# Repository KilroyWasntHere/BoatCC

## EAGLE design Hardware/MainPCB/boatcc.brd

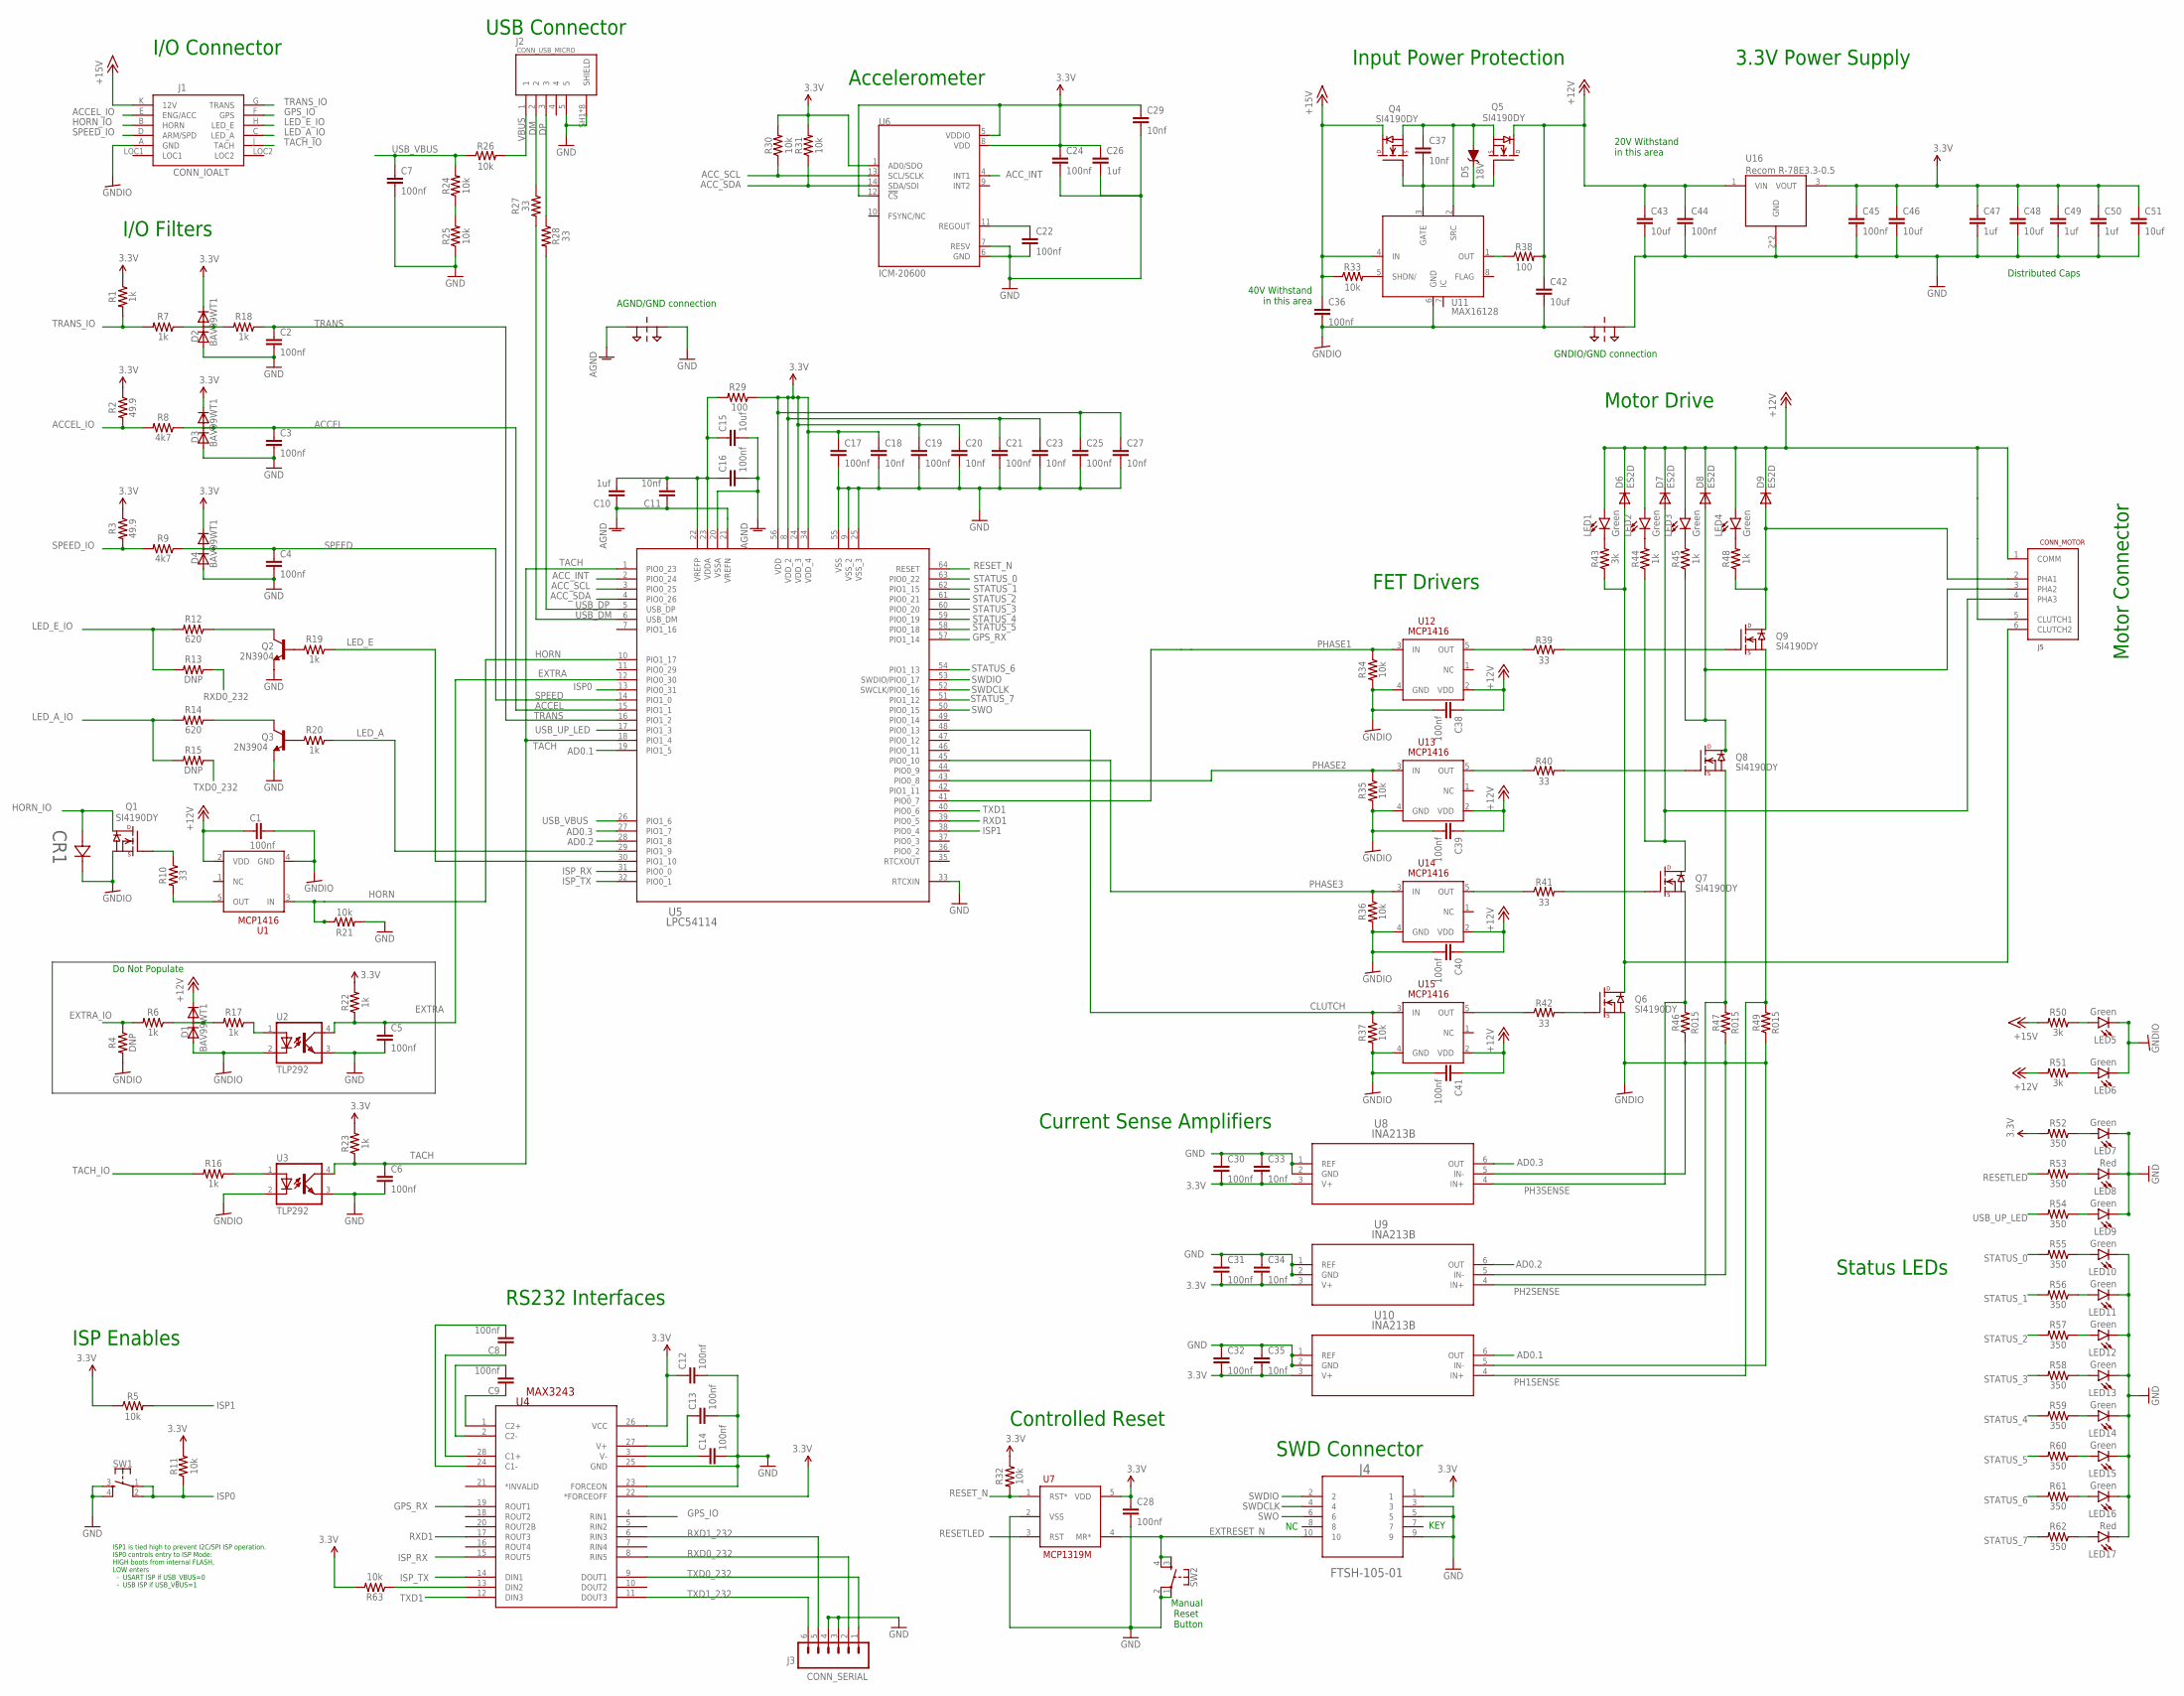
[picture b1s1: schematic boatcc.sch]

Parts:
C1, C2, C3, C4, C5, C6, C7, C8, C9, C12, C13, C14, C16, C17, C19, C21, C22, C24, C25, C28, C30, C31, C32, C36, C38, C39, C40, C41, C44, C45: 100nf; 0805
C10, C26, C47, C49, C50: 1uf; 0805
C11, C18, C20, C23, C27, C29, C33, C34, C35, C37: 10nf; 0805
C15, C42, C43, C46, C48, C51: 10uf; 0805
CR1: SMAJ45CASMASERIES-M; SMASERIES-M; MANUFACTURER_PART_NUMBER SMAJ24CA; DIGI-KEY_PART_NUMBER SMAJ24CALFCT-ND
D1, D2, D3, D4: BAV99WT1; SC70
D5: 18V; SOD-323
D6, D7, D8, D9: ES2D; SMB
J1: CONN_IOALT; CONN_IO
J2: CONN_USB_MICRO; MOLEX_1050170001
J3: CONN_SERIAL; 1X06_LOCK
J4: FTSH-105-01; SAMTEC-FTSH-105-01-X-DV
J5: CONN_MOTOR
LED1, LED2, LED3, LED4, LED5, LED6, LED7, LED9, LED10, LED11, LED12, LED13, LED14, LED15, LED16: Green; LED_0805; DIGI-KEY_PART_NUMBER 732-4986-1-ND
LED8, LED17: Red; LED_0805; DIGI-KEY_PART_NUMBER 732-4984-1-ND
Q1, Q4, Q5, Q6, Q7, Q8, Q9: SI4190DY; SO-8
Q2, Q3: 2N3904; SOT23-3
R1, R6, R7, R16, R17, R18, R19, R20, R22, R23, R44, R45, R48: 1k; 0805
R2, R3: 49.9; 0805
R4, R13, R15: DNP; 0805
R5, R11, R21, R24, R25, R26, R30, R31, R32, R33, R34, R35, R36, R37, R63: 10k; 0805
R8, R9: 4k7; 0805
R10, R27, R28, R39, R40, R41, R42: 33; 0805
R12, R14: 620; 0805
R29, R38: 100; 0805
R43, R50, R51: 3k; 0805
R46, R47, R49: R015; 1206; DIGI-KEY_PART_NUMBER 408-1572-1-ND
R52, R53, R54, R55, R56, R57, R58, R59, R60, R61, R62: 350; 0805
SUPPLY1, SUPPLY2: 2PT_GND_TIE
SW1, SW2: MOMENTARY-SWITCH-SPST-2-SMD-5.2MM; TACTILE_SWITCH_SMD_5.2MM
U1, U12, U13, U14, U15: MCP1416; SOT-23-5_MC-M
U2, U3: TLP292; MINI-FLAT-4; DIGI-KEY_PART_NUMBER TLP292(GB-TPLECT-ND
U4: MAX3243; PW28-M
U5: LPC54114; LQFP64_10X10-M
U6: ICM-20600; PQFN50P250X300X97-14N
U7: MCP1319M; SOT23-5
U8, U9, U10: INA213B; DCK6-M; MANUFACTURER_PART_NUMBER INA213BIDCKR; DIGI-KEY_PART_NUMBER 296-40129-1-ND
U11: MAX16128; UMAX8; MOUSER_PART_NUMBER 700-MAX16128UAACAC+T
U16: Recom R-78E3.3-0.5; D2PACK/A; DIGI-KEY_PART_NUMBER 497-5225-1-ND

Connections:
3.3V: C12.1, C17.1, C18.1, C19.1, C20.1, C21.1, C23.1, C24.1, C25.1, C26.1, C27.1, C28.1, C29.1, C30.2, C31.2, C32.2, C33.2, C34.2, C35.2, C45.1, C46.1, C47.1, C48.1, C49.1, C50.1, C51.1, D2.2 (C), D3.2 (C), D4.2 (C), J4.1, R1.1, R2.1, R3.1, R5.1, R11.2, R22.2, R23.2, R29.1, R30.2, R31.2, R32.1, R52.2, R63.2, U4.22 (*FORCEOFF), U4.26 (VCC), U5.8 (VDD_2), U5.24 (VDD_3), U5.34 (VDD_4), U5.56 (VDD), U6.1 (AD0/SDO), U6.5 (VDDIO), U6.8 (VDD), U6.12 (!CS), U7.5 (VDD), U8.3 (V+), U9.3 (V+), U10.3 (V+), U16.3 (VOUT)
+12V: C1.1, C38.1, C39.1, C40.1, C41.1, C42.1, C43.1, C44.1, D1.2 (C), D6.C, D7.C, D8.C, D9.C, J5.1 (COMM), J5.5 (CLUTCH1), LED1.A, LED2.A, LED3.A, LED4.A, Q5.5 (D), Q5.6 (D), Q5.7 (D), Q5.8 (D), R38.2, R51.2, U1.2 (VDD), U12.2 (VDD), U13.2 (VDD), U14.2 (VDD), U15.2 (VDD), U16.1 (VIN)
+15V: C36.1, J1.K (12V), Q4.5 (D), Q4.6 (D), Q4.7 (D), Q4.8 (D), R33.1, R50.2, U11.4 (IN)
ACCEL: C3.1, D3.3 (AC), R8.1, U5.15 (PIO1_1)
ACCEL_IO: J1.E (ENG/ACC), R2.2, R8.2
ACC_INT: U5.2 (PIO0_24), U6.4 (INT1)
ACC_SCL: R30.1, U5.3 (PIO0_25), U6.13 (SCL/SCLK)
ACC_SDA: R31.1, U5.4 (PIO0_26), U6.14 (SDA/SDI)
AD0.1: U5.19 (PIO1_5), U10.6 (OUT)
AD0.2: U5.28 (PIO1_8), U9.6 (OUT)
AD0.3: U5.27 (PIO1_7), U8.6 (OUT)
AGND: C10.1, C11.1, C15.2, C16.2, SUPPLY1.P$1, U5.20 (VSSA), U5.21 (VREFN)
CLUTCH: R37.1, U5.48 (PIO0_13), U15.3 (IN)
CLUTCH2: D6.A, J5.6 (CLUTCH2), Q6.5 (D), Q6.6 (D), Q6.7 (D), Q6.8 (D), R43.1
DM: J2.2, R27.1
DP: J2.3, R28.1
EXTRA: C5.1, R22.1, U2.4 (COL), U5.12 (PIO0_30)
EXTRA_IO: R4.1, R6.2
EXTRESET_N: J4.10, SW2.3, SW2.4, U7.4 (MR*)
FILTER_IN1: D1.3 (AC), R6.1, R17.2
GND: C2.2, C3.2, C4.2, C5.2, C6.2, C7.2, C12.2, C13.2, C14.2, C17.2, C18.2, C19.2, C20.2, C21.2, C22.2, C23.2, C24.2, C25.2, C26.2, C27.2, C28.2, C29.2, C30.1, C31.1, C32.1, C33.1, C34.1, C35.1, C43.2, C44.2, C45.2, C46.2, C47.2, C48.2, C49.2, C50.2, C51.2, D2.1 (A), D3.1 (A), D4.1 (A), J2.5, J2.SH1 (SHIELD), J2.SH2 (SHIELD), J2.SH3 (SHIELD), J2.SH4 (SHIELD), J2.SH5 (SHIELD), J2.SH6 (SHIELD), J2.SH7 (SHIELD), J2.SH8 (SHIELD), J3.3, J3.4, J4.3, J4.5, J4.9, LED7.C, LED8.C, LED9.C, LED10.C, LED11.C, LED12.C, LED13.C, LED14.C, LED15.C, LED16.C, LED17.C, Q2.2 (E), Q3.2 (E), R21.2, R25.1, SUPPLY1.P$2, SUPPLY2.P$2, SW1.3, SW1.4, SW2.1, SW2.2, U2.3 (EMIT), U3.3 (EMIT), U4.23 (FORCEON), U4.25 (GND), U5.9 (VSS_2), U5.25 (VSS_3), U5.33 (RTCXIN), U5.55 (VSS), U6.6 (GND), U6.7 (RESV), U7.2 (VSS), U8.1 (REF), U8.2 (GND), U9.1 (REF), U9.2 (GND), U10.1 (REF), U10.2 (GND), U16.2 (GND), U16.TAB (GND)
GNDIO: C1.2, C36.2, C38.2, C39.2, C40.2, C41.2, C42.2, CR1.1 (2), D1.1 (A), J1.A (GND), LED5.C, LED6.C, Q1.1 (S), Q1.2 (S), Q1.3 (S), Q6.1 (S), Q6.2 (S), Q6.3 (S), R4.2, R34.2, R35.2, R36.2, R37.2, R46.1, R47.1, R49.1, SUPPLY2.P$1, U1.4 (GND), U2.2 (C), U3.2 (C), U8.5 (IN-), U9.5 (IN-), U10.5 (IN-), U11.6 (GND), U12.4 (GND), U13.4 (GND), U14.4 (GND), U15.4 (GND)
GPS_IO: J1.F (GPS), U4.4 (RIN1)
GPS_RX: U4.19 (ROUT1), U5.57 (PIO1_14)
HORN: R21.1, U1.3 (IN), U5.10 (PIO1_17)
HORN_IO: CR1.2 (1), J1.B (HORN), Q1.5 (D), Q1.6 (D), Q1.7 (D), Q1.8 (D)
INT_PWR: C37.1, D5.A, Q4.1 (S), Q4.2 (S), Q4.3 (S), Q5.1 (S), Q5.2 (S), Q5.3 (S), U11.2 (SRC)
ISP0: R11.1, SW1.1, SW1.2, U5.13 (PIO0_31)
ISP1: R5.2, U5.38 (PIO0_4)
ISP_RX: U4.15 (ROUT5), U5.31 (PIO0_0)
ISP_TX: U4.14 (DIN1), U5.32 (PIO0_1)
LED_A: R20.1, U5.29 (PIO1_9)
LED_A_IO: J1.C (LED_A), R14.2, R15.2
LED_E: R19.1, U5.30 (PIO1_10)
LED_E_IO: J1.H (LED_E), R12.2, R13.2
MOTOR_PHASE_1: D9.A, J5.2 (PHA1), Q9.5 (D), Q9.6 (D), Q9.7 (D), Q9.8 (D), R48.1
MOTOR_PHASE_2: D8.A, J5.3 (PHA2), Q8.5 (D), Q8.6 (D), Q8.7 (D), Q8.8 (D), R45.1
MOTOR_PHASE_3: D7.A, J5.4 (PHA3), Q7.5 (D), Q7.6 (D), Q7.7 (D), Q7.8 (D), R44.1
unnamed: R41.1, U14.5 (OUT)
unnamed: Q2.1 (B), R19.2
unnamed: R10.2, U1.5 (OUT)
unnamed: LED1.C, R43.2
unnamed: Q3.1 (B), R20.2
unnamed: Q1.4 (G), R10.1
unnamed: Q7.4 (G), R41.2
unnamed: LED13.A, R58.1
unnamed: LED12.A, R57.1
unnamed: R17.1, U2.1 (A)
unnamed: R33.2, U11.5 (SHDN/)
unnamed: C37.2, D5.C, Q4.4 (G), Q5.4 (G), U11.3 (GATE)
unnamed: R39.1, U12.5 (OUT)
unnamed: Q9.4 (G), R39.2
unnamed: R40.1, U13.5 (OUT)
unnamed: LED5.A, R50.1
unnamed: LED11.A, R56.1
unnamed: Q8.4 (G), R40.2
unnamed: R38.1, U11.1 (OUT)
unnamed: LED10.A, R55.1
unnamed: LED8.A, R53.1
unnamed: LED7.A, R52.1
unnamed: R42.1, U15.5 (OUT)
unnamed: Q6.4 (G), R42.2
unnamed: LED16.A, R61.1
unnamed: LED2.C, R44.2
unnamed: LED3.C, R45.2
unnamed: LED4.C, R48.2
unnamed: C8.2, U4.24 (C1-)
unnamed: LED6.A, R51.1
unnamed: C8.1, U4.28 (C1+)
unnamed: D2.3 (AC), R7.1, R18.2
unnamed: C9.2, U4.2 (C2-)
unnamed: C9.1, U4.1 (C2+)
unnamed: C22.1, U6.11 (REGOUT)
unnamed: C13.1, U4.27 (V+)
unnamed: LED17.A, R62.1
unnamed: LED9.A, R54.1
unnamed: Q3.3 (C), R14.1
unnamed: Q2.3 (C), R12.1
unnamed: C14.1, U4.3 (V-)
unnamed: R24.1, R25.2
unnamed: R16.1, U3.1 (A)
unnamed: R63.1, U4.13 (DIN2)
unnamed: LED15.A, R60.1
unnamed: LED14.A, R59.1
PH1SENSE: Q9.1 (S), Q9.2 (S), Q9.3 (S), R49.2, U10.4 (IN+)
PH2SENSE: Q8.1 (S), Q8.2 (S), Q8.3 (S), R47.2, U9.4 (IN+)
PH3SENSE: Q7.1 (S), Q7.2 (S), Q7.3 (S), R46.2, U8.4 (IN+)
PHASE1: R34.1, U5.41 (PIO0_7), U12.3 (IN)
PHASE2: R35.1, U5.43 (PIO0_8), U13.3 (IN)
PHASE3: R36.1, U5.45 (PIO0_10), U14.3 (IN)
RESETLED: R53.2, U7.3 (RST)
RESET_N: R32.2, U5.64 (RESET), U7.1 (RST*)
RXD0_232: J3.2, R13.1, U4.8 (RIN5)
RXD1: U4.17 (ROUT3), U5.39 (PIO0_5)
RXD1_232: J3.5, U4.6 (RIN3)
SPEED: C4.1, D4.3 (AC), R9.1, U5.14 (PIO1_0)
SPEED_IO: J1.D (ARM/SPD), R3.2, R9.2
STATUS_0: R55.2, U5.63 (PIO0_22)
STATUS_1: R56.2, U5.62 (PIO1_15)
STATUS_2: R57.2, U5.61 (PIO0_21)
STATUS_3: R58.2, U5.60 (PIO0_20)
STATUS_4: R59.2, U5.59 (PIO0_19)
STATUS_5: R60.2, U5.58 (PIO0_18)
STATUS_6: R61.2, U5.54 (PIO1_13)
STATUS_7: R62.2, U5.51 (PIO1_12)
SWDCLK: J4.4, U5.52 (SWCLK/PIO0_16)
SWDIO: J4.2, U5.53 (SWDIO/PIO0_17)
SWO: J4.6, U5.50 (PIO0_15)
TACH: C6.1, R23.1, U3.4 (COL), U5.1 (PIO0_23), U5.18 (PIO1_4)
TACH_IO: J1.J (TACH), R16.2
TRANS: C2.1, R18.1, U5.16 (PIO1_2)
TRANS_IO: J1.G (TRANS), R1.2, R7.2
TXD0_232: J3.1, R15.1, U4.9 (DOUT1)
TXD1: U4.12 (DIN3), U5.40 (PIO0_6)
TXD1_232: J3.6, U4.11 (DOUT3)
USB_DM: R27.2, U5.6 (USB_DM)
USB_DP: R28.2, U5.5 (USB_DP)
USB_UP_LED: R54.2, U5.17 (PIO1_3)
USB_VBUS: C7.1, R24.2, R26.1, U5.26 (PIO1_6)
VBUS: J2.1, R26.2
VDDA: C10.2, C11.2, C15.1, C16.1, R29.2, U5.22 (VREFP), U5.23 (VDDA)

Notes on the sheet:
Manual Reset Button
3.3V Power Supply
Motor Drive
FET Drivers
Status LEDs
Controlled Reset
I/O Connector
Accelerometer
Input Power Protection
Motor Connector
I/O Filters
RS232 Interfaces
20V Withstand in this area
SWD Connector
ISP Enables
ISP1 is tied high to prevent I2C/SPI ISP operation. ISP0 controls entry to ISP Mode: HIGH boots from internal FLASH, LOW enters - USART ISP if USB_VBUS=0 - USB ISP if USB_VBUS=1
Distributed Caps
USB Connector
KEY
GNDIO/GND connection
AGND/GND connection
Current Sense Amplifiers
40V Withstand in this area
Do Not Populate

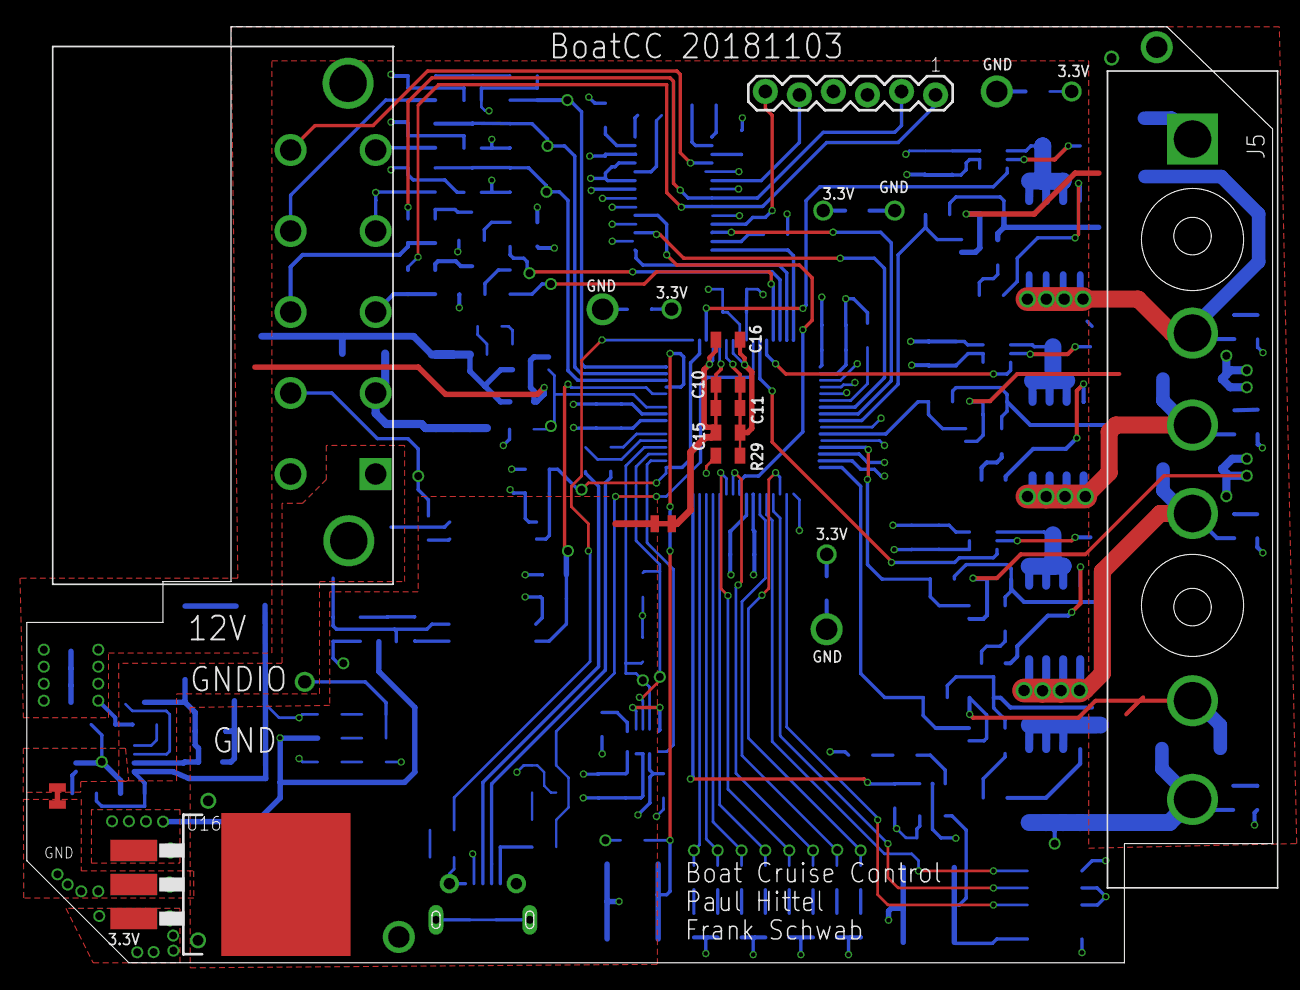
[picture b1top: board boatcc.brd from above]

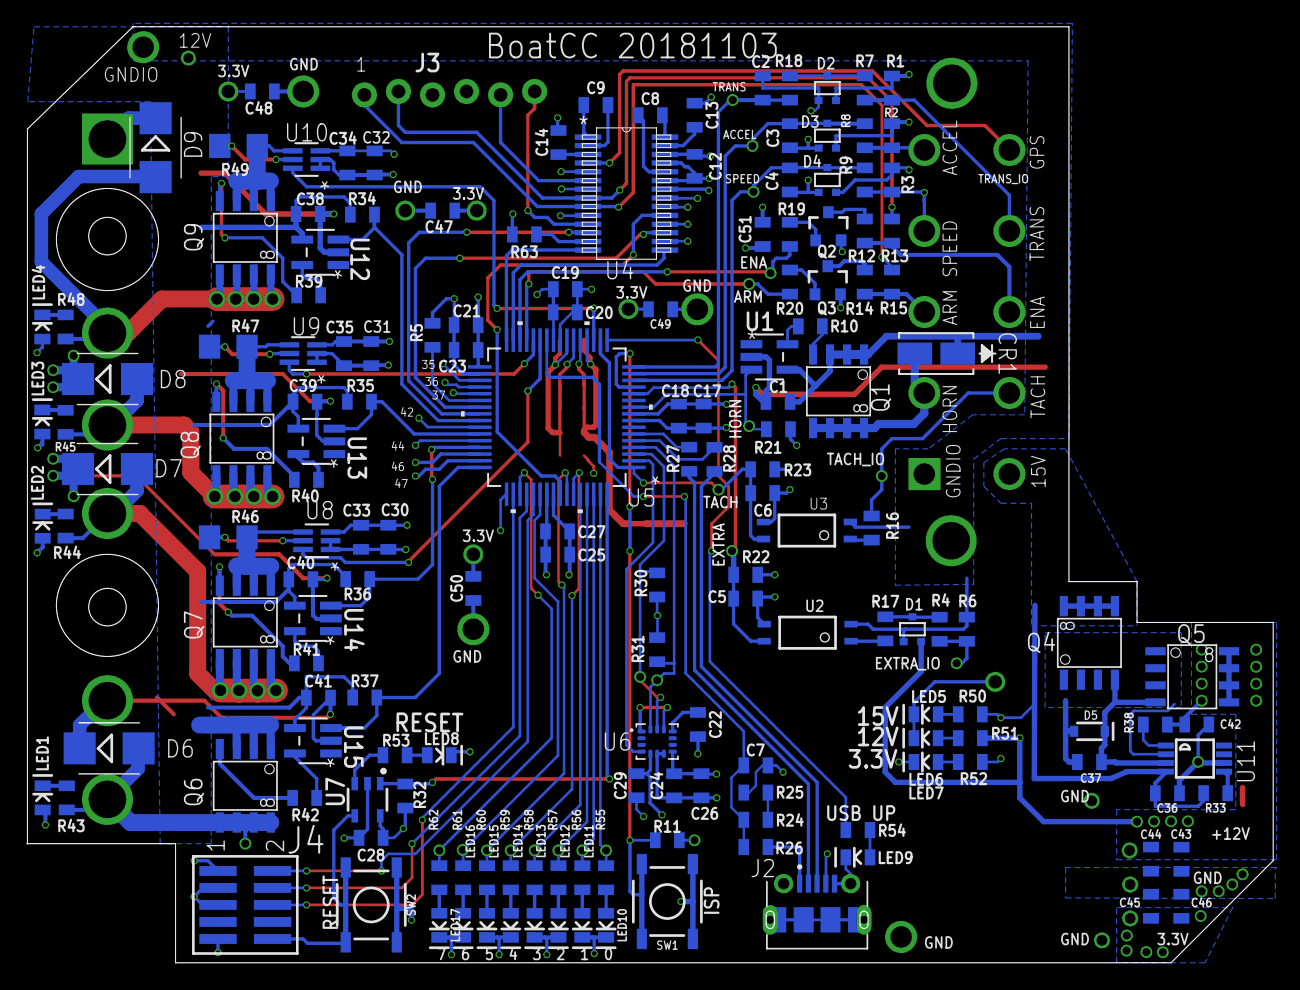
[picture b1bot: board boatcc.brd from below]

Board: 4 copper layers, 93.0 x 69.8 mm, 175 parts (164 on the bottom side), 121 nets.

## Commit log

2018-11-04 Hardware Designs
